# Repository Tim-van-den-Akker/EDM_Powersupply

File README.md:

# EDM_Powersupply

Using KiCad 8.0.2

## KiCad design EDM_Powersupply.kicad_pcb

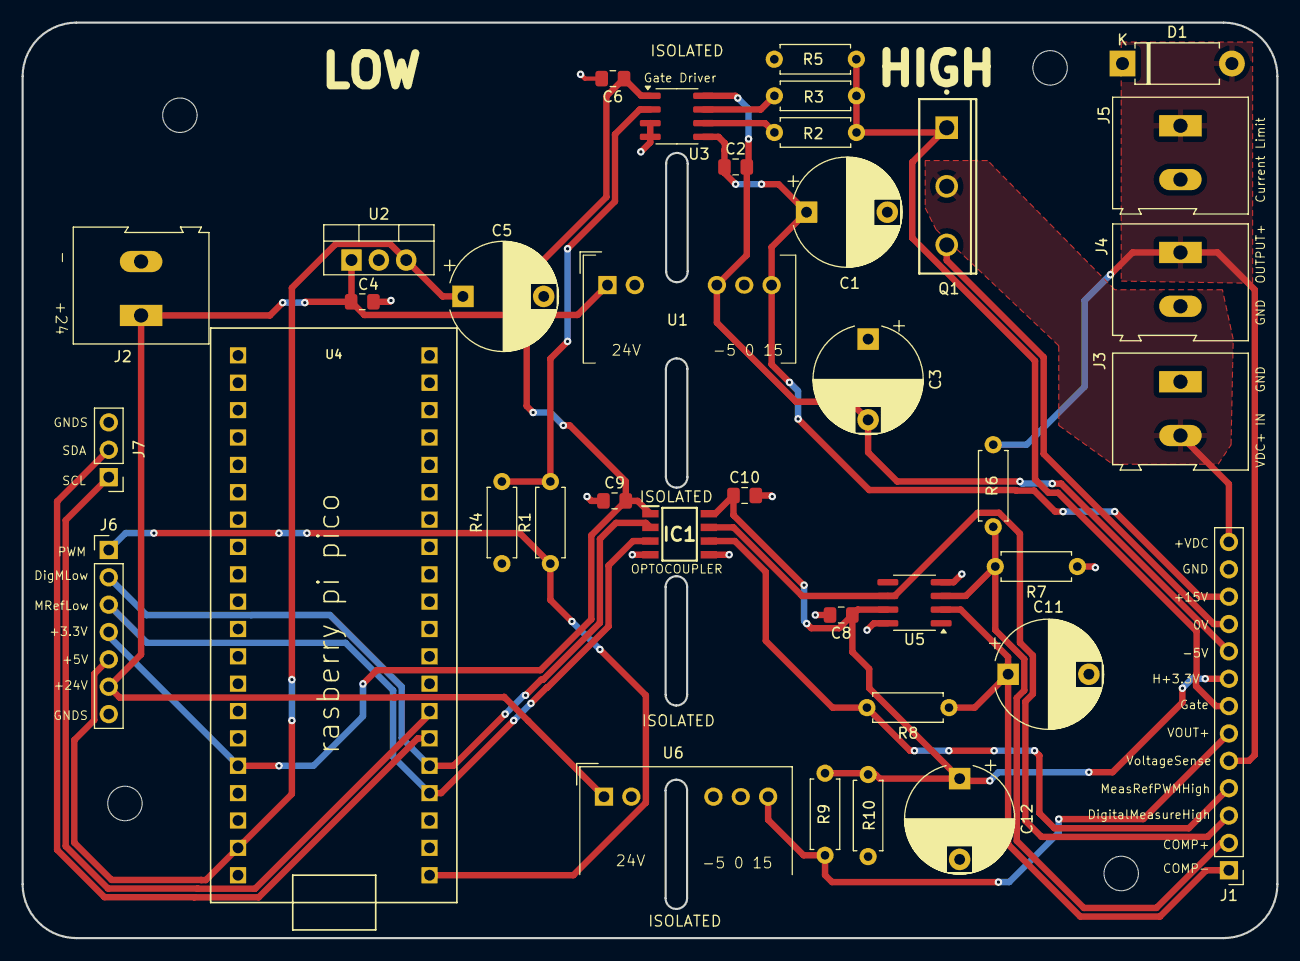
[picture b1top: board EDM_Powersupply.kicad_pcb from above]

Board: 2 copper layers, 116.5 x 85.0 mm, 41 parts (0 on the bottom side), 25 nets.

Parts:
C1, C3, C5, C11: 1u; CP_Radial_D10.0mm_P7.50mm
C2, C6, C9, C10: 100n; C_0805_2012Metric_Pad1.18x1.45mm_HandSolder
C4: 0.33u; C_0805_2012Metric_Pad1.18x1.45mm_HandSolder
C8: 0.1u; C_0805_2012Metric_Pad1.18x1.45mm_HandSolder
C12: 2.2u; CP_Radial_D10.0mm_P7.50mm
D1: D; D_DO-15_P10.16mm_Horizontal
H1, H2, H3, H4: MountingHole; MountingHole_3.2mm_M3
IC1: ACSL-7210-06RE
J1: Conn_01x13_Pin; PinHeader_1x13_P2.54mm_Vertical
J2, J3, J4, J5: Screw_Terminal_01x02; TerminalBlock_Altech_AK300-2_P5.00mm
J6: Conn_01x07_Pin; PinHeader_1x07_P2.54mm_Vertical
J7: Conn_01x03_Pin; PinHeader_1x03_P2.54mm_Vertical
Q1: IPW65R037C6
R1: 100; R_Axial_DIN0207_L6.3mm_D2.5mm_P7.62mm_Horizontal
R2, R3: 1.2; R_Axial_DIN0207_L6.3mm_D2.5mm_P7.62mm_Horizontal
R4, R5: 10k; R_Axial_DIN0207_L6.3mm_D2.5mm_P7.62mm_Horizontal
R6: 100k; R_Axial_DIN0207_L6.3mm_D2.5mm_P7.62mm_Horizontal
R7: 2.2k; R_Axial_DIN0207_L6.3mm_D2.5mm_P7.62mm_Horizontal
R8: 3.3k; R_Axial_DIN0207_L6.3mm_D2.5mm_P7.62mm_Horizontal
R9: 47k; R_Axial_DIN0207_L6.3mm_D2.5mm_P7.62mm_Horizontal
R10: 13k; R_Axial_DIN0207_L6.3mm_D2.5mm_P7.62mm_Horizontal
U1, U6: MGJ2D241505SC; Converter_DCDC_Murata_MGJ2DxxxxxxSC_THT
U2: L7805; TO-220-3_Vertical
U3: STGAP2SM; SOIC-8_3.9x4.9mm_P1.27mm
U4: RASPBERRY_PI_PICO
U5: TLV3501AID; SOIC-8_3.9x4.9mm_P1.27mm

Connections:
0V: C1.2, C3.1, D1.1 (K), J1.10, J5.2, Q1.3 (SOURCE), R5.1, U1.6 (0V)
+3.3V: C6.1, C9.2, IC1.1 (VDD1), J6.4, U3.1 (VDD), U4.3V3
+5V: C5.1, J6.5, U2.3 (OUT), U4.VSYS
+15V: C1.1, C2.1, J1.11, U1.7 (+VOUT), U3.5 (VH)
+24V: C4.1, J2.1, J6.6, U1.1 (+VIN), U2.1 (IN), U6.1 (+VIN)
+VDC: J1.13, J3.2, Q1.2 (DRAIN)
+VOUT: J1.6, R9.1, U6.7 (+VOUT)
-5V: C2.2, C3.2, J1.9, U1.5 (-VOUT), U3.8 (GNDISO)
/GOFF: R3.1, U3.7 (GOFF)
/GON: R2.1, U3.6 (GON)
/IN+: R1.2, R4.2, U3.2 (IN+)
Comp+: J1.2, R6.2, R7.2, U5.3 (+)
Comp-: C11.1, J1.1, R8.1, U5.2 (-)
DigitalMeasureHigh: IC1.7 (VI_A), J1.3, U5.6
DigitalMeasureLow: IC1.2 (VOA), J6.2, U4.GP3
GND: C8.2, C10.2, C11.2, C12.2, IC1.5 (GND_2), J1.12, J3.1, J4.2, R7.1, R10.2, U5.4 (V-), U5.8 (SHDN), U6.6 (0V)
GNDS: C4.2, C5.2, C6.2, C9.1, IC1.4 (GND_1), J2.2, J6.7, J7.3, R4.1, U1.2 (-VIN), U2.2 (GND), U3.3 (IN-), U3.4 (GND), U4.GND, U4.GND2, U4.GND3, U4.GND4, U4.GND5, U4.GND6, U4.GND7, U6.2 (-VIN)
Gate: J1.7, Q1.1 (GATE), R2.2, R3.2, R5.2
H+3.3V: C8.1, C10.1, C12.1, IC1.8 (VDD2), J1.8, R9.2, R10.1, U5.7 (V+)
MeasRefPWMHigh: IC1.6 (VOB), J1.4, R8.2
MeasRefPWMLow: IC1.3 (VI_B), J6.3, U4.GP2
PWM: J6.1, R1.1, U4.GP0
SCL: J7.1, U4.GP5
SDA: J7.2, U4.GP4
VoltageSense: D1.2 (A), J1.5, J4.1, J5.1, R6.1

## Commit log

2024-04-29 Empty Project
2024-04-29 Basic NMOSFET with working simulation
2024-05-02 working simulation
2024-05-06 Simulation 7-may
2024-05-07 Simulation fixed + some default NMOS testing files
2024-05-07 Added model + footprint for IPW NMOS
2024-05-07 Fixed small mistake in simulation + added the IPW NMOS properly
2024-05-09 Added the UCC gate driver sim model + footprint
2024-05-10 improved layout
2024-05-11 EDM_Powersupply in LTSpice :)
2024-05-13 microcontroller support
    microcontroller with voltage devider for analog and digital
2024-05-14 ltspice
2024-05-14 Ltspice schematic V3 added
    Low-side driving with isolation. Correct fet selected now
2024-05-15 Signal isolation concept
2024-05-15 changed to high side switching
2024-05-21 Ltspice update high-side switching
2024-05-21 switched some things around, mainly gnds
2024-05-22 Full Reordering and added test pads
2024-05-22 Updated ERC
2024-05-22 Investigated oscillations from voltage across R_currentlimiting after t_off
2024-05-23 Oscillaties weg
2024-05-23 dom haakje
2024-05-23 Of nee toch niet
2024-05-23 Kicad oscillatie fix met diode
2024-05-23 good
2024-05-23 PCB Done?
2024-05-23 final?
2024-05-26 stash
2024-05-29 Ltspice simulations with diode and cap
2024-05-31 ltspice update
2024-06-03 Ignore this
2024-06-12 LTspice update: frequency of oscillation (fet model adjusted)
2024-06-19 Ltspice 100V
